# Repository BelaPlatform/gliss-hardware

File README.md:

# gliss-hardware

You can find the source KiCad files for the Gliss module in this repository. This project is open hardware and under the Creative Commons Share Alike license 4.0.
The firmware can be found in the repository https://github.com/BelaPlatform/gliss-firmware

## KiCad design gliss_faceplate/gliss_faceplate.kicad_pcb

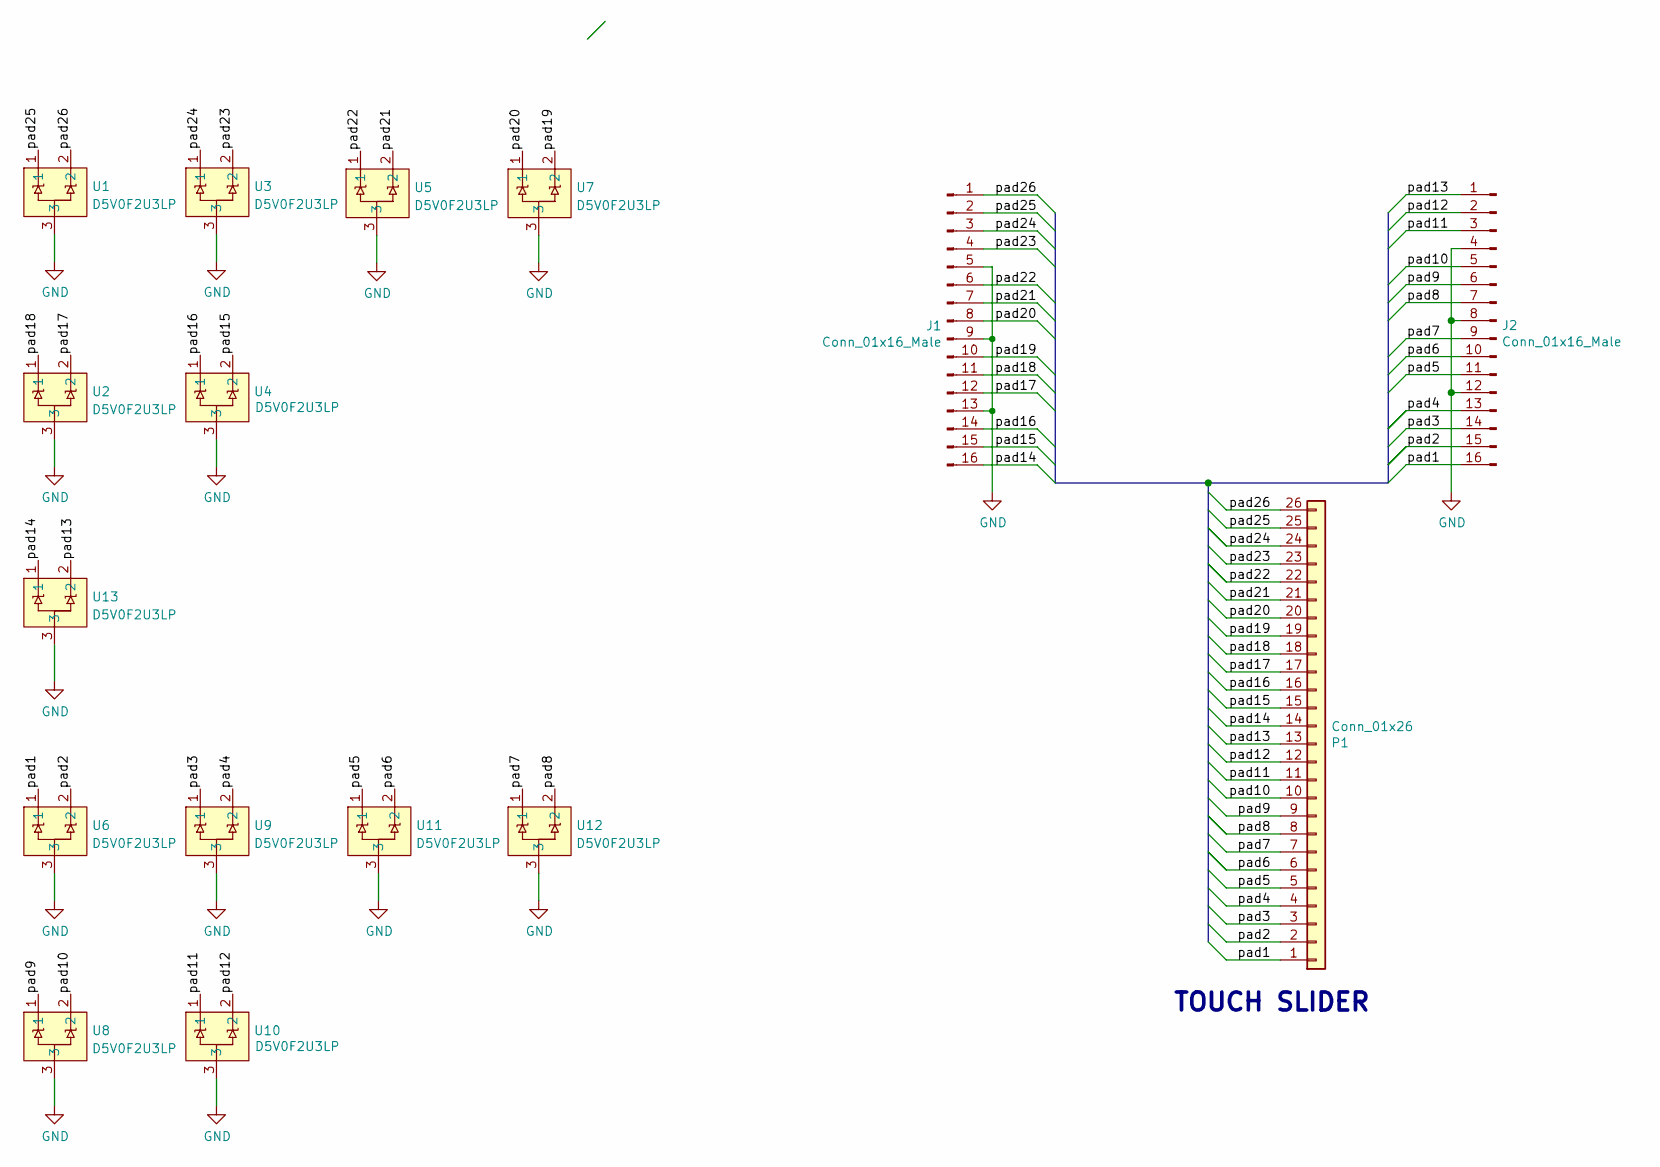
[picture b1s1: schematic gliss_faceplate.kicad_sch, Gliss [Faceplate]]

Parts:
J1, J2: Conn_01x16_Male; PinHeader_1x16_P2.54mm_Vertical_SMD_Pin1Right
P1: Conn_01x26; TouchSlider-26_89.5x17.8mm
U1, U2, U3, U4, U5, U6, U7, U8, U9, U10, U11, U12, U13: D5V0F2U3LP; Diodes_DFN1006-3

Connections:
/pad1: J2.16, P1.1, U6.1
/pad2: J2.15, P1.2, U6.2
/pad3: J2.14, P1.3, U9.1
/pad4: J2.13, P1.4, U9.2
/pad5: J2.11, P1.5, U11.1
/pad6: J2.10, P1.6, U11.2
/pad7: J2.9, P1.7, U12.1
/pad8: J2.7, P1.8, U12.2
/pad9: J2.6, P1.9, U8.1
/pad10: J2.5, P1.10, U8.2
/pad11: J2.3, P1.11, U10.1
/pad12: J2.2, P1.12, U10.2
/pad13: J2.1, P1.13
/pad14: J1.16, P1.14, U13.1
/pad15: J1.15, P1.15, U4.2
/pad16: J1.14, P1.16, U4.1
/pad17: J1.12, P1.17, U2.2
/pad18: J1.11, P1.18, U2.1
/pad19: J1.10, P1.19, U7.2
/pad20: J1.8, P1.20, U7.1
/pad21: J1.7, P1.21, U5.2
/pad22: J1.6, P1.22, U5.1
/pad23: J1.4, P1.23, U3.2
/pad24: J1.3, P1.24, U3.1
/pad25: J1.2, P1.25, U1.1
/pad26: J1.1, P1.26, U1.2
GND: J1.5, J1.9, J1.13, J2.4, J2.8, J2.12, U1.3, U2.3, U3.3, U4.3, U5.3, U6.3, U7.3, U8.3, U9.3, U10.3, U11.3, U12.3, U13.3

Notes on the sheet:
TOUCH SLIDER

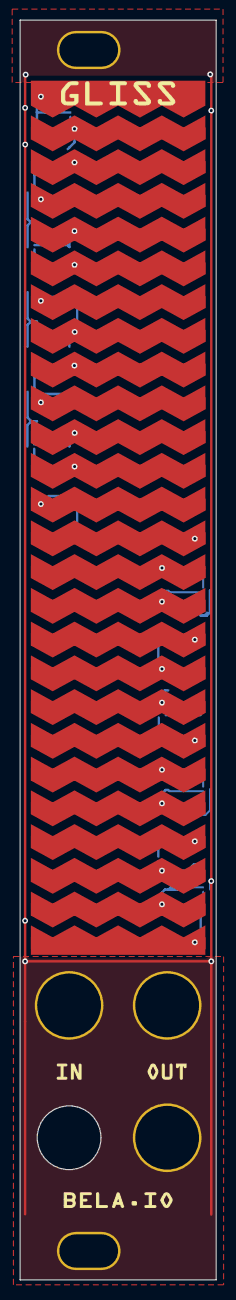
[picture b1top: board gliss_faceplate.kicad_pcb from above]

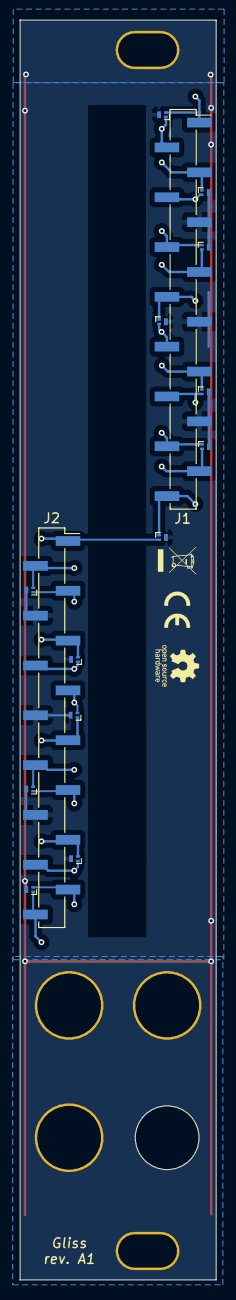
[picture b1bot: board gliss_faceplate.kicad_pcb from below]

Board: 2 copper layers, 20.0 x 128.5 mm, 17 parts (15 on the bottom side), 27 nets.

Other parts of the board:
outline: Val**; gliss_edge_silkscreen

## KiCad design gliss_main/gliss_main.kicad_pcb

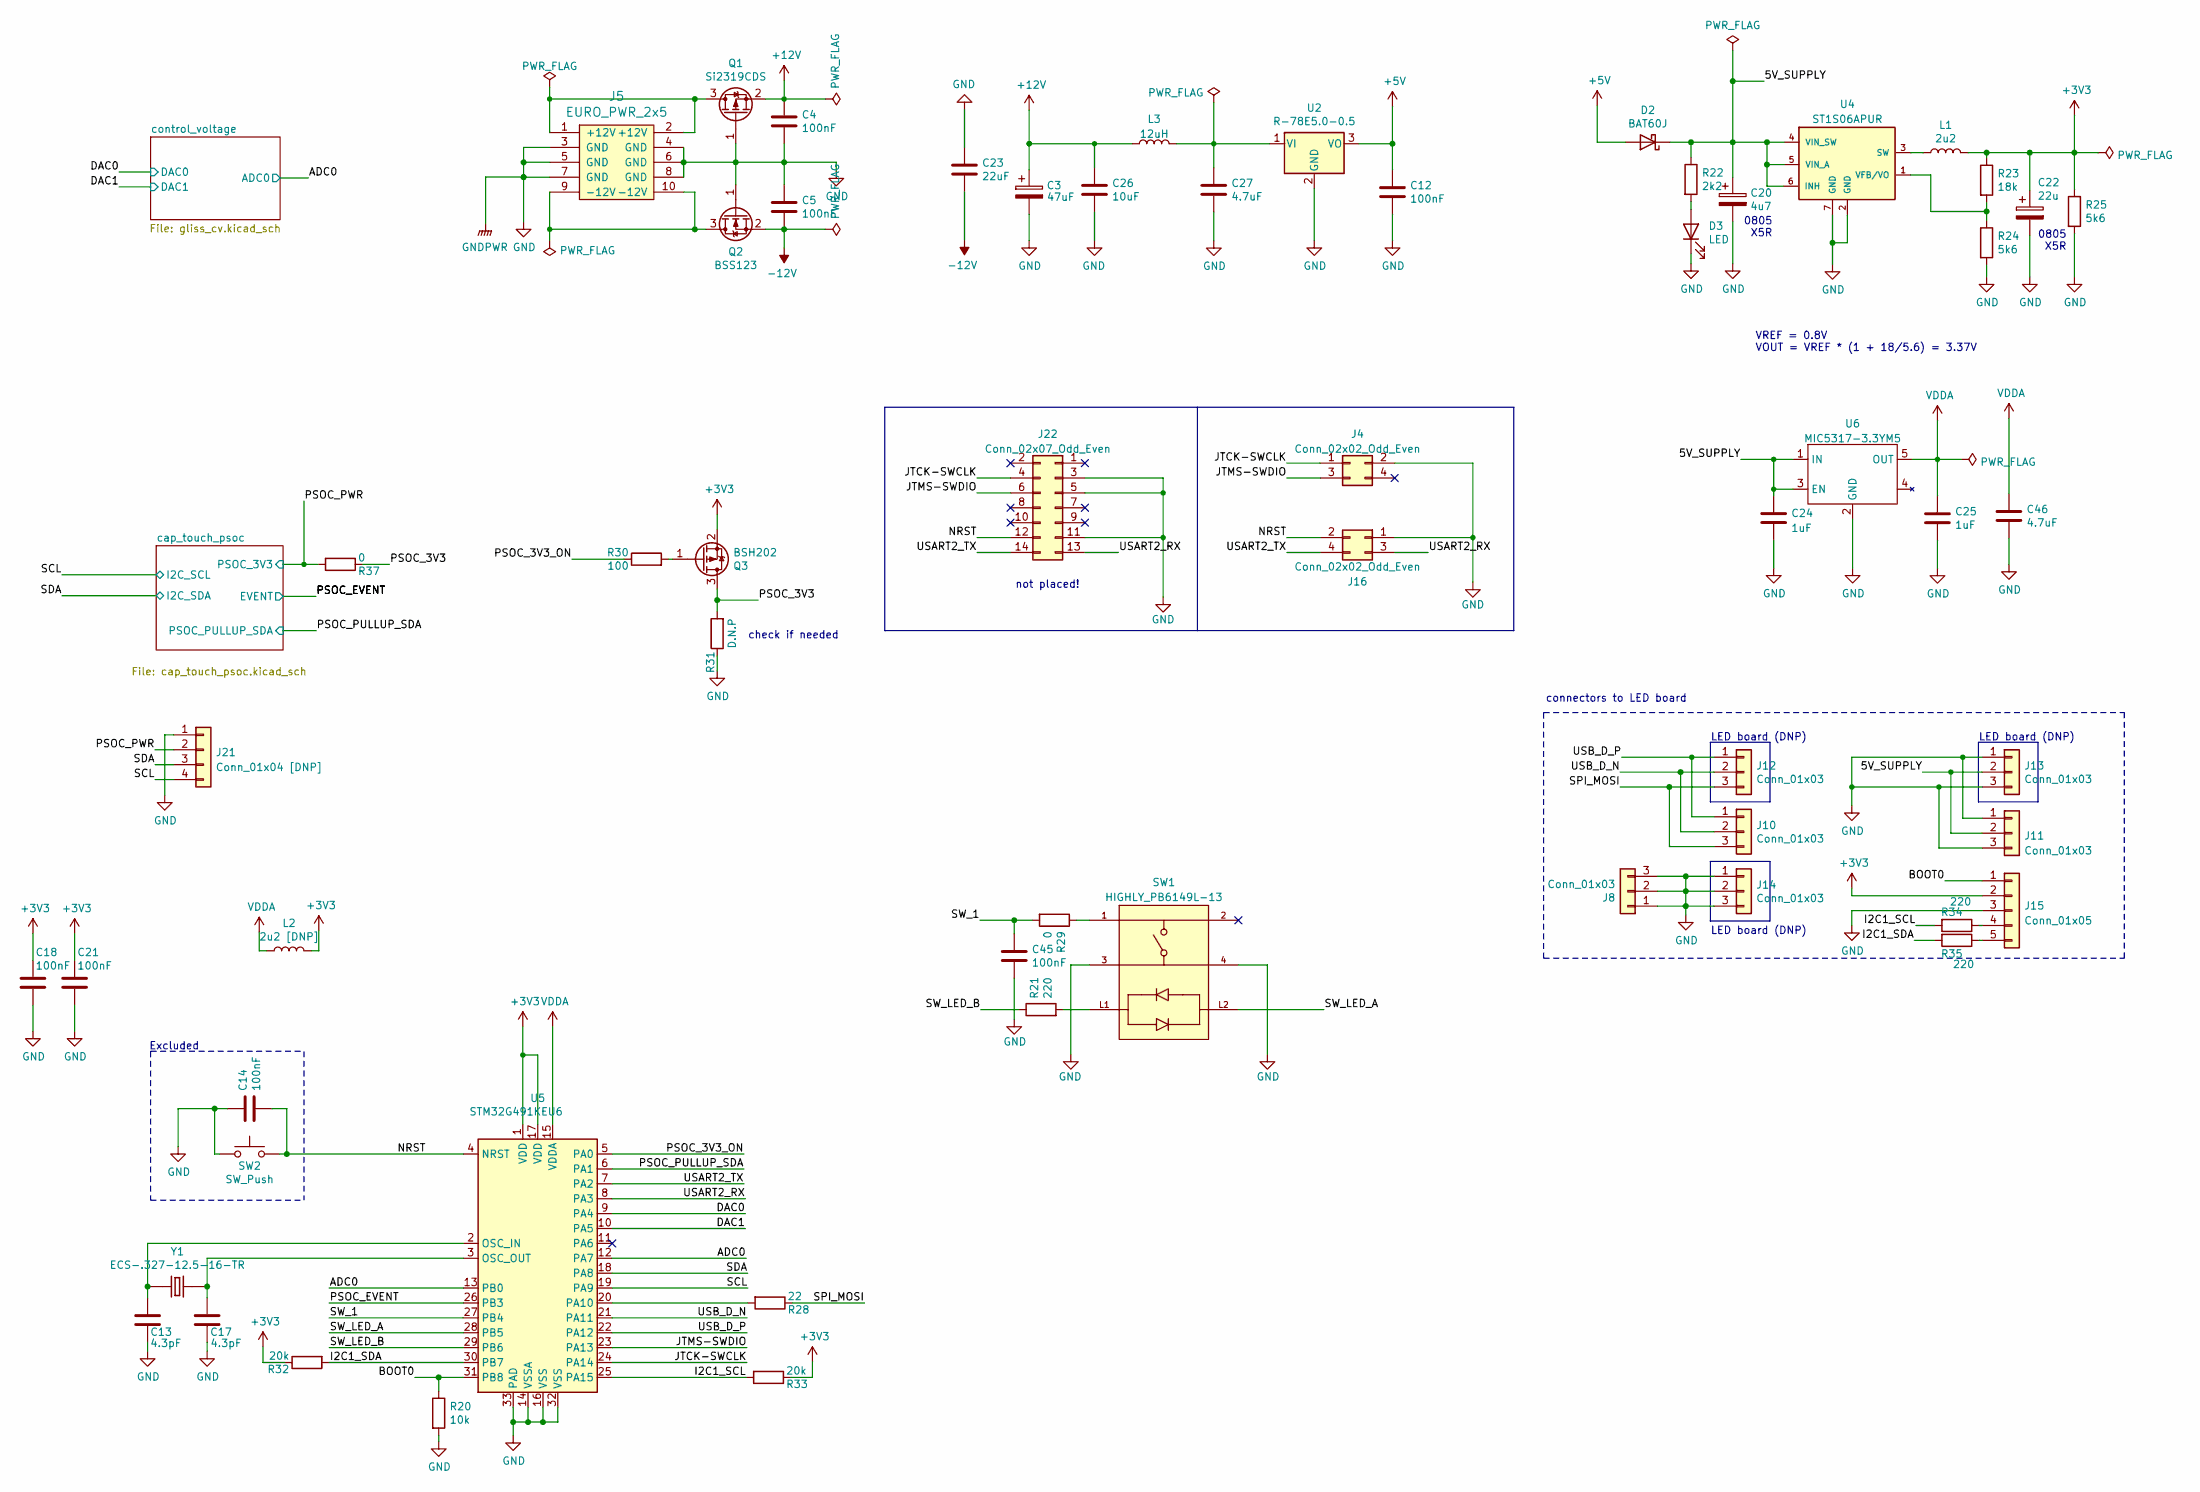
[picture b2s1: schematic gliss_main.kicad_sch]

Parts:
C3: 47uF; CP_Radial_D5.0mm_P2.00mm
C4, C5: 100nF; C_0805_2012Metric
C12: 100nF; C_0603_1608Metric
C13, C17: 4.3pF; C_0402_1005Metric
C14, C18, C21, C45: 100nF; C_0402_1005Metric
C20: 4u7; C_0805_2012Metric
C22: 22u; C_0805_2012Metric
C23: 22uF; C_0805_2012Metric
C24, C25: 1uF; C_0402_1005Metric
C26: 10uF; C_0603_1608Metric
C27: 4.7uF; C_0603_1608Metric
C46: 4.7uF; C_0402_1005Metric
D2: BAT60J; D_SOD-323
D3: LED; LED_0603_1608Metric
J4, J16: Conn_02x02_Odd_Even; PinHeader_2x02_P1.27mm_Vertical
J5: EURO_PWR_2x5; PinHeader_2x05_P2.54mm_Vertical
J8, J10, J11: Conn_01x03; PinHeader_1x03_P2.54mm_Vertical
J12, J13, J14: Conn_01x03; PinHeader_1x03_P2.54mm_Vertical_SMD_Pin1Left
J15: Conn_01x05; PinHeader_1x05_P2.54mm_Vertical
J21: Conn_01x04 [DNP]; PinHeader_1x04_P1.27mm_Vertical
J22: Conn_02x07_Odd_Even; PinHeader_2x07_P1.27mm_Vertical
L1: 2u2; L_0603_1608Metric
L2: 2u2 [DNP]; L_0603_1608Metric
L3: 12uH; L_1210_3225Metric
Q1: Si2319CDS; SOT-23
Q2: BSS123; SOT-23
Q3: BSH202; SOT-23
R20: 10k; R_0402_1005Metric
R21, R34, R35: 220; R_0402_1005Metric
R22: 2k2; R_0402_1005Metric
R23: 18k; R_0402_1005Metric
R24, R25: 5k6; R_0402_1005Metric
R28: 22; R_0402_1005Metric
R29, R37: 0; R_0402_1005Metric
R30: 100; R_0402_1005Metric
R31: D.N.P; R_0402_1005Metric
R32, R33: 20k; R_0402_1005Metric
SW1: HIGHLY_PB6149L-13; HIGHLY_PB6149L_v4
SW2: SW_Push; SW_SPST_B3U-1000P
U2: R-78E5.0-0.5; R-78-xxx-0.5
U4: ST1S06APUR; DFN-6-1EP_3x3mm_P0.95mm_EP1.7x2.6mm
U5: STM32G491KEU6; QFN-32-1EP_5x5mm_P0.5mm_EP3.45x3.45mm
U6: MIC5317-3.3YM5; TSOT-23-5
Y1: ECS-.327-12.5-16-TR; XTAL_ECS-.327-12.5-16-TR

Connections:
+3V3: C18.1, C21.1, C22.1, J15.2, L1.2, L2.2, Q3.2 (S), R23.1, R25.1, R32.1, R33.1, U5.1 (VDD), U5.17 (VDD); also elsewhere on the board
+5V: C12.1, D2.2 (A), U2.3 (VO)
+12V: C3.1, C4.1, C26.1, L3.1, Q1.2 (S); also elsewhere on the board
-12V: C5.2, C23.2, Q2.2 (S); also elsewhere on the board
/5V_SUPPLY: C20.1, C24.1, D2.1 (K), J11.2, J13.2, R22.1, U4.4 (VIN_SW), U4.5 (VIN_A), U4.6 (INH), U6.1 (IN), U6.3 (EN)
/ADC0: U5.12 (PA7), U5.13 (PB0); also elsewhere on the board
/BOOT0: J15.1, R20.1, U5.31 (PB8)
/DAC0: U5.9 (PA4); also elsewhere on the board
/DAC1: U5.10 (PA5); also elsewhere on the board
/I2C1_SCL: R33.2, R34.2, U5.25 (PA15)
/I2C1_SDA: R32.2, R35.2, U5.30 (PB7)
/JTCK-SWCLK: J4.1, J22.4, U5.24 (PA14)
/JTMS-SWDIO: J4.3, J22.6, U5.23 (PA13)
/NRST: C14.2, J16.2, J22.12, SW2.2, U5.4 (NRST)
/PSOC_3V3: Q3.3 (D), R31.2, R37.1
/PSOC_3V3_ON: R30.1, U5.5 (PA0)
/PSOC_EVENT: U5.26 (PB3); also elsewhere on the board
/PSOC_PULLUP_SDA: U5.6 (PA1); also elsewhere on the board
/PSOC_PWR: J21.2, R37.2; also elsewhere on the board
/SCL: J21.4, U5.19 (PA9); also elsewhere on the board
/SDA: J21.3, U5.18 (PA8); also elsewhere on the board
/SPI_MOSI: J10.3, J12.3, R28.1
/SW_1: C45.1, R29.2, U5.27 (PB4)
/SW_LED_A: SW1.L2, U5.28 (PB5)
/SW_LED_B: R21.1, U5.29 (PB6)
/USART2_RX: J16.3, J22.13, U5.8 (PA3)
/USART2_TX: J16.4, J22.14, U5.7 (PA2)
/USB_D_N: J10.2, J12.2, U5.21 (PA11)
/USB_D_P: J10.1, J12.1, U5.22 (PA12)
GND: C3.2, C4.2, C5.1, C12.2, C13.2, C14.1, C17.2, C18.2, C20.2, C21.2, C22.2, C23.1, C24.2, C25.2, C26.2, C27.2, C45.2, C46.2, D3.1 (K), J4.2, J5.3 (GND), J5.4 (GND), J5.5 (GND), J5.6 (GND), J5.7 (GND), J5.8 (GND), J8.1, J8.2, J8.3, J11.1, J11.3, J13.1, J13.3, J14.1, J14.2, J14.3, J15.3, J16.1, J21.1, J22.3, J22.5, J22.11, Q1.1 (G), Q2.1 (G), R20.2, R24.2, R25.2, R31.1, SW1.3, SW1.4, SW2.1, U2.2 (GND), U4.2 (GND), U4.7 (GND), U5.14 (VSSA), U5.16 (VSS), U5.32 (VSS), U5.33 (PAD), U6.2 (GND); also elsewhere on the board
unnamed: C13.1, U5.2 (OSC_IN), Y1.1
unnamed: C17.1, U5.3 (OSC_OUT), Y1.2
unnamed: C27.1, L3.2, U2.1 (VI)
unnamed: D3.2 (A), R22.2
unnamed: J5.1 (+12V), J5.2 (+12V), Q1.3 (D)
unnamed: J5.9 (-12V), J5.10 (-12V), Q2.3 (D)
unnamed: J15.4, R34.1
unnamed: J15.5, R35.1
unnamed: L1.1, U4.3 (SW)
unnamed: Q3.1 (G), R30.2
unnamed: R21.2, SW1.L1
unnamed: R23.2, R24.1, U4.1 (VFB/VO)
unnamed: R28.2, U5.20 (PA10)
unnamed: R29.1, SW1.1
VDDA: C25.1, C46.1, L2.1, U5.15 (VDDA), U6.5 (OUT)

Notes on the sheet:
Excluded
LED board (DNP)
0805 X5R
connectors to LED board
VREF = 0.8V VOUT = VREF * (1 + 18/5.6) = 3.37V
check if needed
not placed!

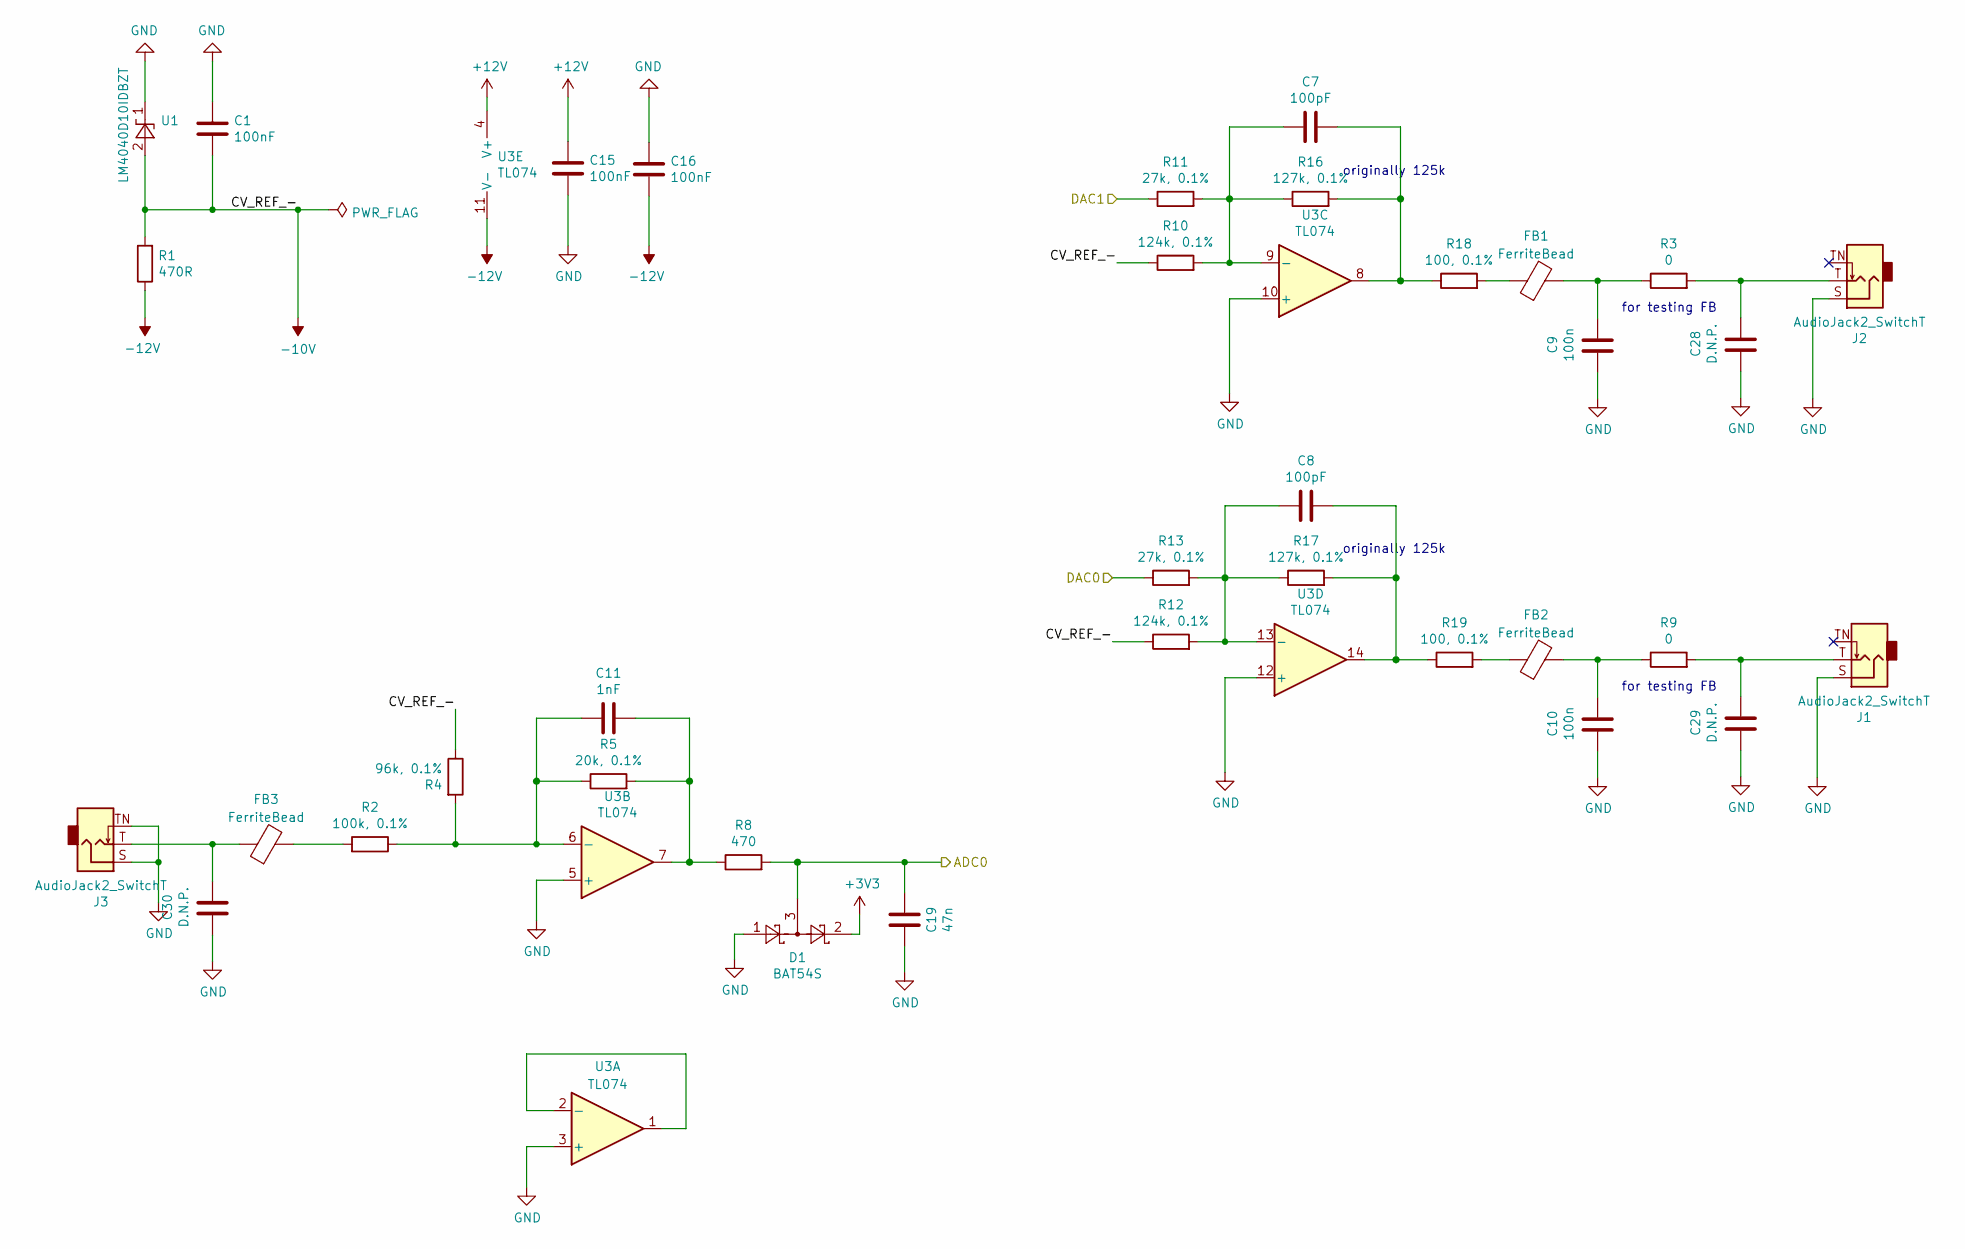
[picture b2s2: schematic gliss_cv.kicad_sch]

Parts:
C1, C15, C16: 100nF; C_0402_1005Metric
C7, C8: 100pF; C_0402_1005Metric
C9, C10: 100n; C_0402_1005Metric
C11: 1nF; C_0402_1005Metric
C19: 47n; C_0402_1005Metric
C28, C29, C30: D.N.P.; C_0402_1005Metric
D1: BAT54S; SOT-23
FB1, FB2, FB3: FerriteBead; L_0402_1005Metric
J1, J2, J3: AudioJack2_SwitchT; Jack_3.5mm_QingPu_WQP-PJ398SM_Vertical_CircularHoles
R1: 470R; R_0402_1005Metric
R2: 100k, 0.1%; R_0402_1005Metric
R3, R9: 0; R_0402_1005Metric
R4: 96k, 0.1%; R_0402_1005Metric
R5: 20k, 0.1%; R_0402_1005Metric
R8: 470; R_0402_1005Metric
R10, R12: 124k, 0.1%; R_0402_1005Metric
R11, R13: 27k, 0.1%; R_0402_1005Metric
R16, R17: 127k, 0.1%; R_0402_1005Metric
R18, R19: 100, 0.1%; R_0402_1005Metric
U1: LM4040D10IDBZT; SOT-23
U3: TL074

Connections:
+3V3: D1.2; also elsewhere on the board
+12V: C15.1, U3.4 (V+); also elsewhere on the board
-10V: C1.2, R1.2, R4.1, R10.1, R12.1, U1.2 (A)
-12V: C16.2, R1.1, U3.11 (V-); also elsewhere on the board
/ADC0: C19.2, D1.3, R8.2; also elsewhere on the board
/DAC0: R13.1; also elsewhere on the board
/DAC1: R11.1; also elsewhere on the board
GND: C1.1, C9.1, C10.1, C15.2, C16.1, C19.1, C28.1, C29.1, C30.1, D1.1, J1.S, J2.S, J3.S, J3.TN, U1.1 (K), U3.3 (+), U3.5 (+), U3.10 (+), U3.12 (+); also elsewhere on the board
unnamed: C7.1, R10.2, R11.2, R16.1, U3.9 (-)
unnamed: C7.2, R16.2, R18.1, U3.8
unnamed: C8.1, R12.2, R13.2, R17.1, U3.13 (-)
unnamed: C8.2, R17.2, R19.1, U3.14
unnamed: C9.2, FB1.2, R3.1
unnamed: C10.2, FB2.2, R9.1
unnamed: C11.1, R2.1, R4.2, R5.1, U3.6 (-)
unnamed: C11.2, R5.2, R8.1, U3.7
unnamed: C28.2, J2.T, R3.2
unnamed: C29.2, J1.T, R9.2
unnamed: C30.2, FB3.1, J3.T
unnamed: FB1.1, R18.2
unnamed: FB2.1, R19.2
unnamed: FB3.2, R2.2
unnamed: U3.1, U3.2 (-)

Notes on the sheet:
originally 125k
for testing FB

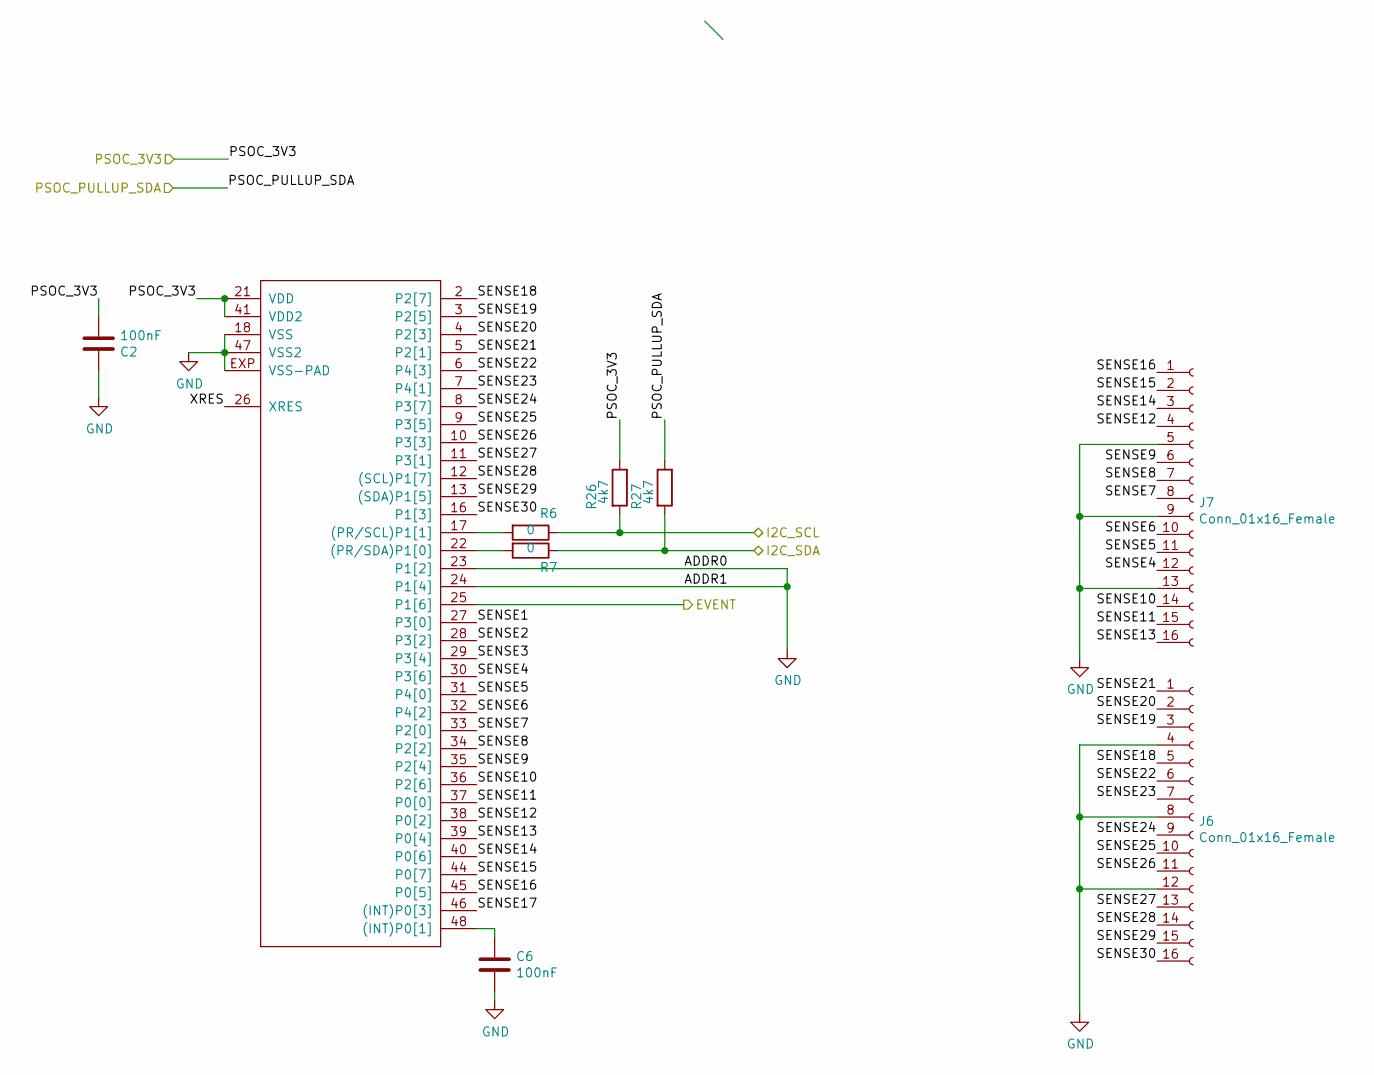
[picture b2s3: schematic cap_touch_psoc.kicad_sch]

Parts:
C2, C6: 100nF; C_0402_1005Metric
J6, J7: Conn_01x16_Female; PinHeader_1x16_P2.54mm_Vertical
R6, R7: 0; R_0402_1005Metric
R26, R27: 4k7; R_0402_1005Metric
U30: CY8C206X6A; QFN48-LEADS

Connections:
/PSOC_EVENT: U30.25 (P1[6]); also elsewhere on the board
/PSOC_PULLUP_SDA: R27.1; also elsewhere on the board
/PSOC_PWR: C2.2, R26.1, U30.21 (VDD), U30.41 (VDD2); also elsewhere on the board
/SCL: R6.1, R26.2; also elsewhere on the board
/SDA: R7.1, R27.2; also elsewhere on the board
/cap_touch_psoc/SENSE1: U30.27 (P3[0])
/cap_touch_psoc/SENSE2: U30.28 (P3[2])
/cap_touch_psoc/SENSE3: U30.29 (P3[4])
/cap_touch_psoc/SENSE4: J7.12, U30.30 (P3[6])
/cap_touch_psoc/SENSE5: J7.11, U30.31 (P4[0])
/cap_touch_psoc/SENSE6: J7.10, U30.32 (P4[2])
/cap_touch_psoc/SENSE7: J7.8, U30.33 (P2[0])
/cap_touch_psoc/SENSE8: J7.7, U30.34 (P2[2])
/cap_touch_psoc/SENSE9: J7.6, U30.35 (P2[4])
/cap_touch_psoc/SENSE10: J7.14, U30.36 (P2[6])
/cap_touch_psoc/SENSE11: J7.15, U30.37 (P0[0])
/cap_touch_psoc/SENSE12: J7.4, U30.38 (P0[2])
/cap_touch_psoc/SENSE13: J7.16, U30.39 (P0[4])
/cap_touch_psoc/SENSE14: J7.3, U30.40 (P0[6])
/cap_touch_psoc/SENSE15: J7.2, U30.44 (P0[7])
/cap_touch_psoc/SENSE16: J7.1, U30.45 (P0[5])
/cap_touch_psoc/SENSE17: U30.46 ((INT)P0[3])
/cap_touch_psoc/SENSE18: J6.5, U30.2 (P2[7])
/cap_touch_psoc/SENSE19: J6.3, U30.3 (P2[5])
/cap_touch_psoc/SENSE20: J6.2, U30.4 (P2[3])
/cap_touch_psoc/SENSE21: J6.1, U30.5 (P2[1])
/cap_touch_psoc/SENSE22: J6.6, U30.6 (P4[3])
/cap_touch_psoc/SENSE23: J6.7, U30.7 (P4[1])
/cap_touch_psoc/SENSE24: J6.9, U30.8 (P3[7])
/cap_touch_psoc/SENSE25: J6.10, U30.9 (P3[5])
/cap_touch_psoc/SENSE26: J6.11, U30.10 (P3[3])
/cap_touch_psoc/SENSE27: J6.13, U30.11 (P3[1])
/cap_touch_psoc/SENSE28: J6.14, U30.12 ((SCL)P1[7])
/cap_touch_psoc/SENSE29: J6.15, U30.13 ((SDA)P1[5])
/cap_touch_psoc/SENSE30: J6.16, U30.16 (P1[3])
/cap_touch_psoc/XRES: U30.26 (XRES)
GND: C2.1, C6.2, J6.4, J6.8, J6.12, J7.5, J7.9, J7.13, U30.18 (VSS), U30.23 (P1[2]), U30.24 (P1[4]), U30.47 (VSS2), U30.EXP (VSS-PAD); also elsewhere on the board
unnamed: C6.1, U30.48 ((INT)P0[1])
unnamed: R6.2, U30.17 ((PR/SCL)P1[1])
unnamed: R7.2, U30.22 ((PR/SDA)P1[0])

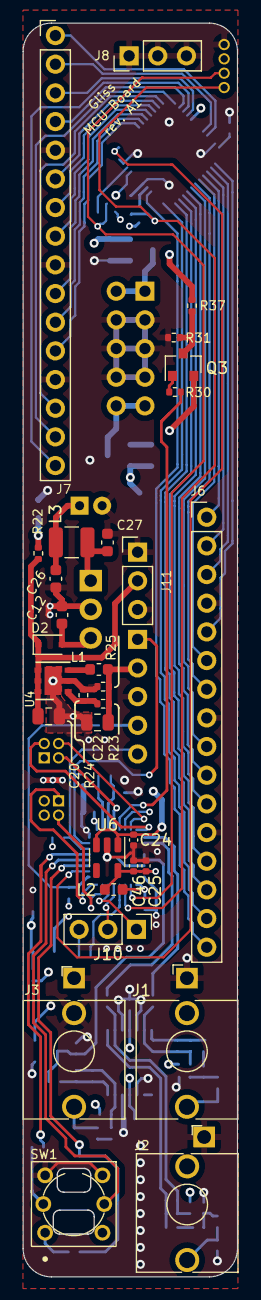
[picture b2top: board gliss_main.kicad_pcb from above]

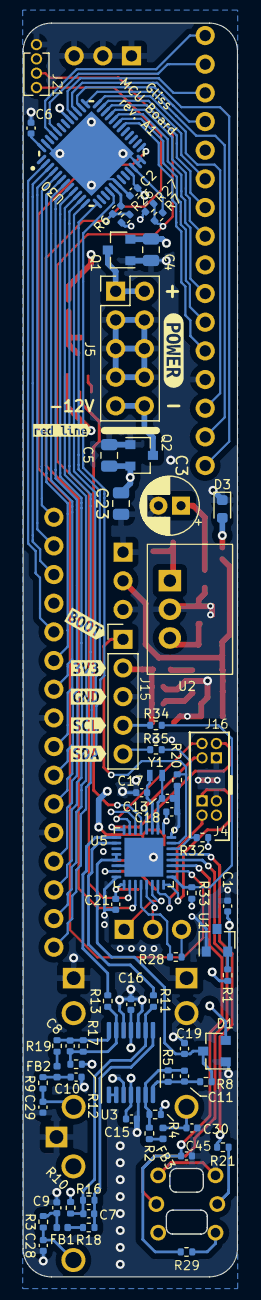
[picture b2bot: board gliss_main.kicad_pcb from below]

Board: 4 copper layers, 19.0 x 111.1 mm, 107 parts (75 on the bottom side), 90 nets.

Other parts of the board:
kibuzzard-639244A3: G***; kibuzzard-639244A3
kibuzzard-639247C2: G***; kibuzzard-639247C2
kibuzzard-6392461D: G***; kibuzzard-6392461D
kibuzzard-6392462F: G***; kibuzzard-6392462F
kibuzzard-6392472E: G***; kibuzzard-6392472E
kibuzzard-63924611: G***; kibuzzard-63924611
kibuzzard-63924626: G***; kibuzzard-63924626
outline: Val**; gliss_edge_silkscreen_user_graphics

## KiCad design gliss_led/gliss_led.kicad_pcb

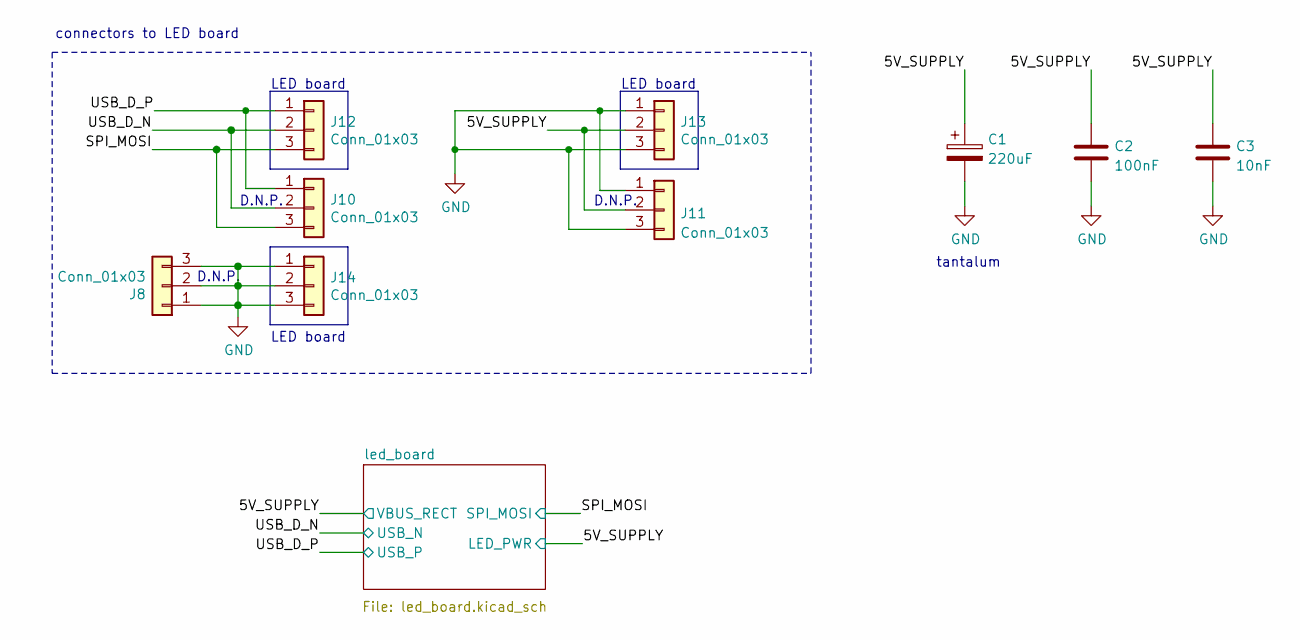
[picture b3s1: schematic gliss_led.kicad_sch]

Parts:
C1: 220uF; CP_EIA-3528-15_AVX-H
C2: 100nF; C_0402_1005Metric
C3: 10nF; C_0402_1005Metric
J8, J10, J11: Conn_01x03; PinHeader_1x03_P2.54mm_Vertical
J12, J13, J14: Conn_01x03; PinHeader_1x03_P2.54mm_Vertical_SMD_Pin1Left

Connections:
/5V_SUPPLY: C1.1, C2.1, C3.1, J11.2, J13.2; also elsewhere on the board
/SPI_MOSI: J10.3, J12.3; also elsewhere on the board
/USB_D_N: J10.2, J12.2; also elsewhere on the board
/USB_D_P: J10.1, J12.1; also elsewhere on the board
GND: C1.2, C2.2, C3.2, J8.1, J8.2, J8.3, J11.1, J11.3, J13.1, J13.3, J14.1, J14.2, J14.3; also elsewhere on the board

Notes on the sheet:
LED board
LED board
D.N.P.
connectors to LED board
tantalum

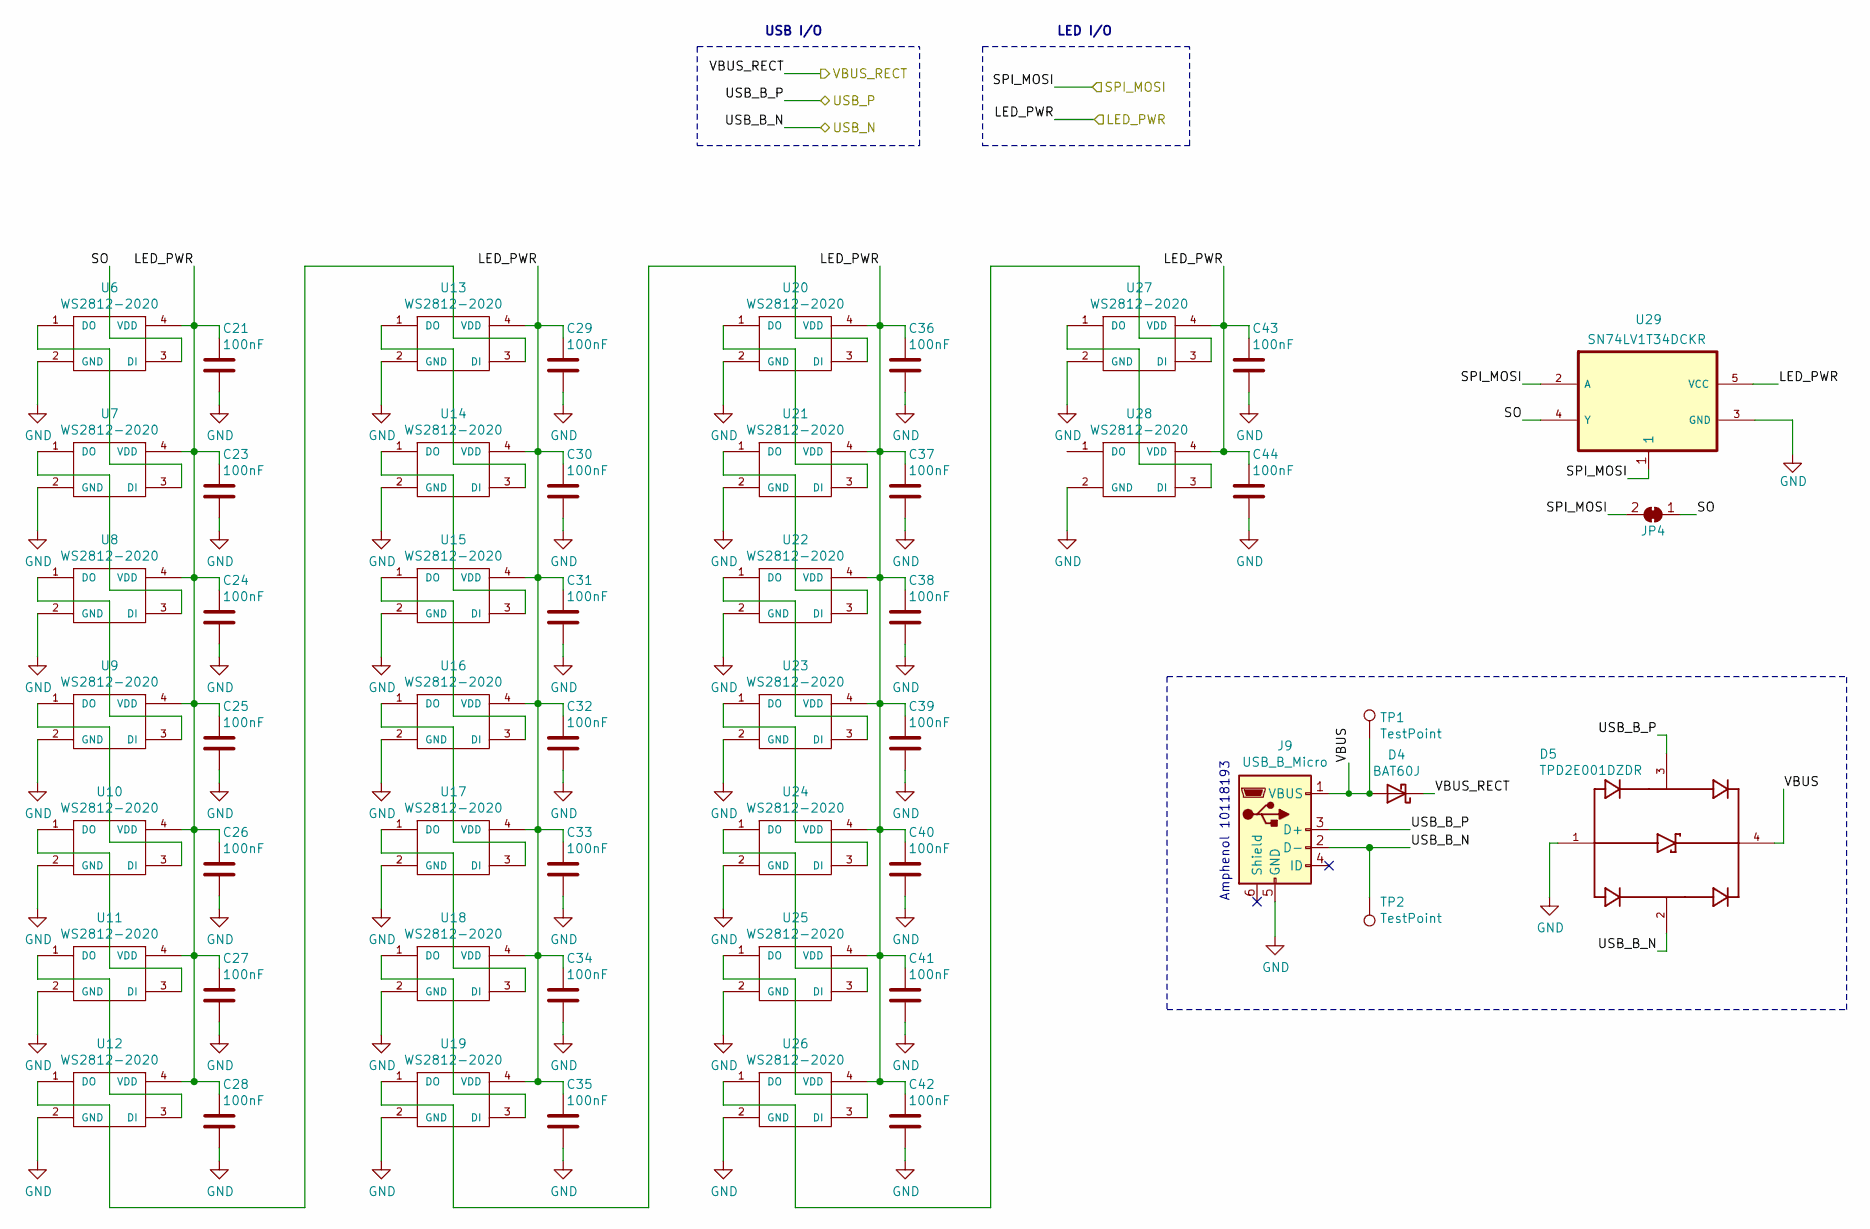
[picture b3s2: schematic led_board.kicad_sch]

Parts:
C21, C23, C24, C25, C26, C27, C28, C29, C30, C31, C32, C33, C34, C35, C36, C37, C38, C39, C40, C41, C42, C43, C44: 100nF; C_0402_1005Metric
D4: BAT60J; D_SOD-323
D5: TPD2E001DZDR; SOT192P237X122-4N; PARTREV I
J9: USB_B_Micro; USB_Micro-B_Amphenol_10118194_Horizontal
JP4: SolderJumper_2_Bridged; SolderJumper-2_P1.3mm_Open_TrianglePad1.0x1.5mm
TP1, TP2: TestPoint; TestPoint_Pad_D1.5mm
U6, U7, U8, U9, U10, U11, U12, U13, U14, U15, U16, U17, U18, U19, U20, U21, U22, U23, U24, U25, U26, U27, U28: WS2812-2020; LED_WS2812-2020
U29: SN74LV1T34DCKR; SOT65P210X110-5N

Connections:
/5V_SUPPLY: C21.1, C23.1, C24.1, C25.1, C26.1, C27.1, C28.1, C29.1, C30.1, C31.1, C32.1, C33.1, C34.1, C35.1, C36.1, C37.1, C38.1, C39.1, C40.1, C41.1, C42.1, C43.1, C44.1, D4.1 (K), U6.4 (VDD), U7.4 (VDD), U8.4 (VDD), U9.4 (VDD), U10.4 (VDD), U11.4 (VDD), U12.4 (VDD), U13.4 (VDD), U14.4 (VDD), U15.4 (VDD), U16.4 (VDD), U17.4 (VDD), U18.4 (VDD), U19.4 (VDD), U20.4 (VDD), U21.4 (VDD), U22.4 (VDD), U23.4 (VDD), U24.4 (VDD), U25.4 (VDD), U26.4 (VDD), U27.4 (VDD), U28.4 (VDD), U29.5 (VCC); also elsewhere on the board
/SPI_MOSI: JP4.2 (B), U29.1, U29.2 (A); also elsewhere on the board
/USB_D_N: D5.2, J9.2 (D-), TP2.1; also elsewhere on the board
/USB_D_P: D5.3, J9.3 (D+); also elsewhere on the board
/led_board/SO: JP4.1 (A), U6.3 (DI), U29.4 (Y)
/led_board/VBUS: D4.2 (A), D5.4, J9.1 (VBUS), TP1.1
GND: C21.2, C23.2, C24.2, C25.2, C26.2, C27.2, C28.2, C29.2, C30.2, C31.2, C32.2, C33.2, C34.2, C35.2, C36.2, C37.2, C38.2, C39.2, C40.2, C41.2, C42.2, C43.2, C44.2, D5.1, J9.5 (GND), U6.2 (GND), U7.2 (GND), U8.2 (GND), U9.2 (GND), U10.2 (GND), U11.2 (GND), U12.2 (GND), U13.2 (GND), U14.2 (GND), U15.2 (GND), U16.2 (GND), U17.2 (GND), U18.2 (GND), U19.2 (GND), U20.2 (GND), U21.2 (GND), U22.2 (GND), U23.2 (GND), U24.2 (GND), U25.2 (GND), U26.2 (GND), U27.2 (GND), U28.2 (GND), U29.3 (GND); also elsewhere on the board
unnamed: U6.1 (DO), U7.3 (DI)
unnamed: U7.1 (DO), U8.3 (DI)
unnamed: U8.1 (DO), U9.3 (DI)
unnamed: U10.1 (DO), U11.3 (DI)
unnamed: U9.1 (DO), U10.3 (DI)
unnamed: U11.1 (DO), U12.3 (DI)
unnamed: U12.1 (DO), U13.3 (DI)
unnamed: U13.1 (DO), U14.3 (DI)
unnamed: U14.1 (DO), U15.3 (DI)
unnamed: U15.1 (DO), U16.3 (DI)
unnamed: U16.1 (DO), U17.3 (DI)
unnamed: U17.1 (DO), U18.3 (DI)
unnamed: U18.1 (DO), U19.3 (DI)
unnamed: U19.1 (DO), U20.3 (DI)
unnamed: U20.1 (DO), U21.3 (DI)
unnamed: U21.1 (DO), U22.3 (DI)
unnamed: U22.1 (DO), U23.3 (DI)
unnamed: U23.1 (DO), U24.3 (DI)
unnamed: U24.1 (DO), U25.3 (DI)
unnamed: U25.1 (DO), U26.3 (DI)
unnamed: U26.1 (DO), U27.3 (DI)
unnamed: U27.1 (DO), U28.3 (DI)

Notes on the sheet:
LED I/O
USB I/O
Amphenol 10118193

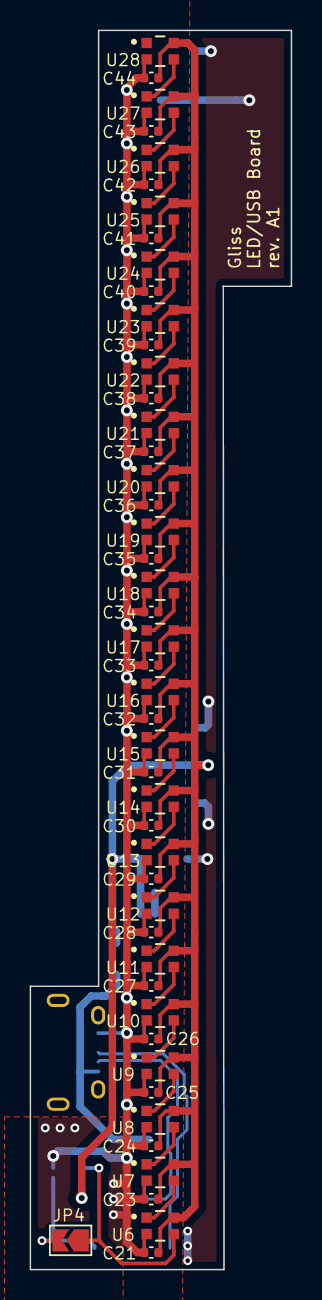
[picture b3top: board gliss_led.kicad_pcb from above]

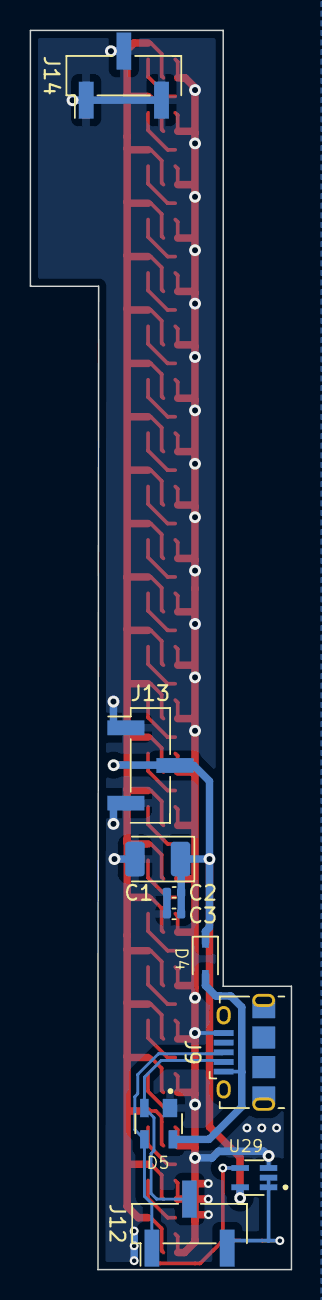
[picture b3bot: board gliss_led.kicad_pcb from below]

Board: 2 copper layers, 17.6 x 83.6 mm, 57 parts (10 on the bottom side), 29 nets.

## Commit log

2023-10-27 v1.0
